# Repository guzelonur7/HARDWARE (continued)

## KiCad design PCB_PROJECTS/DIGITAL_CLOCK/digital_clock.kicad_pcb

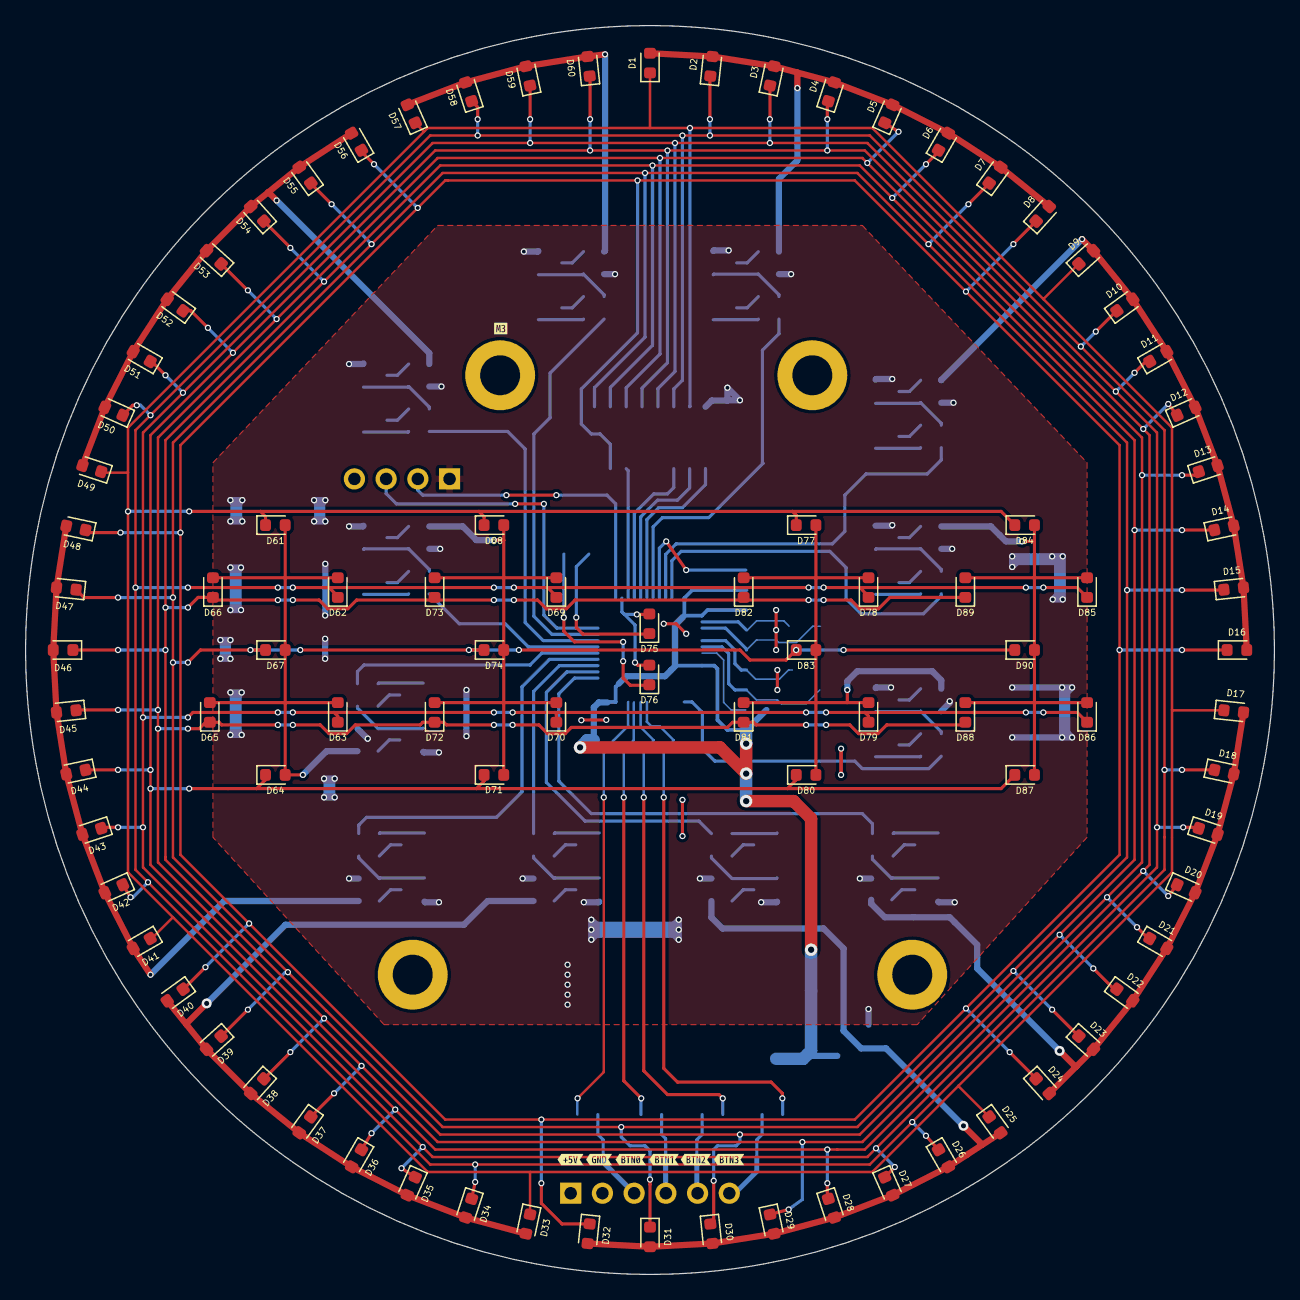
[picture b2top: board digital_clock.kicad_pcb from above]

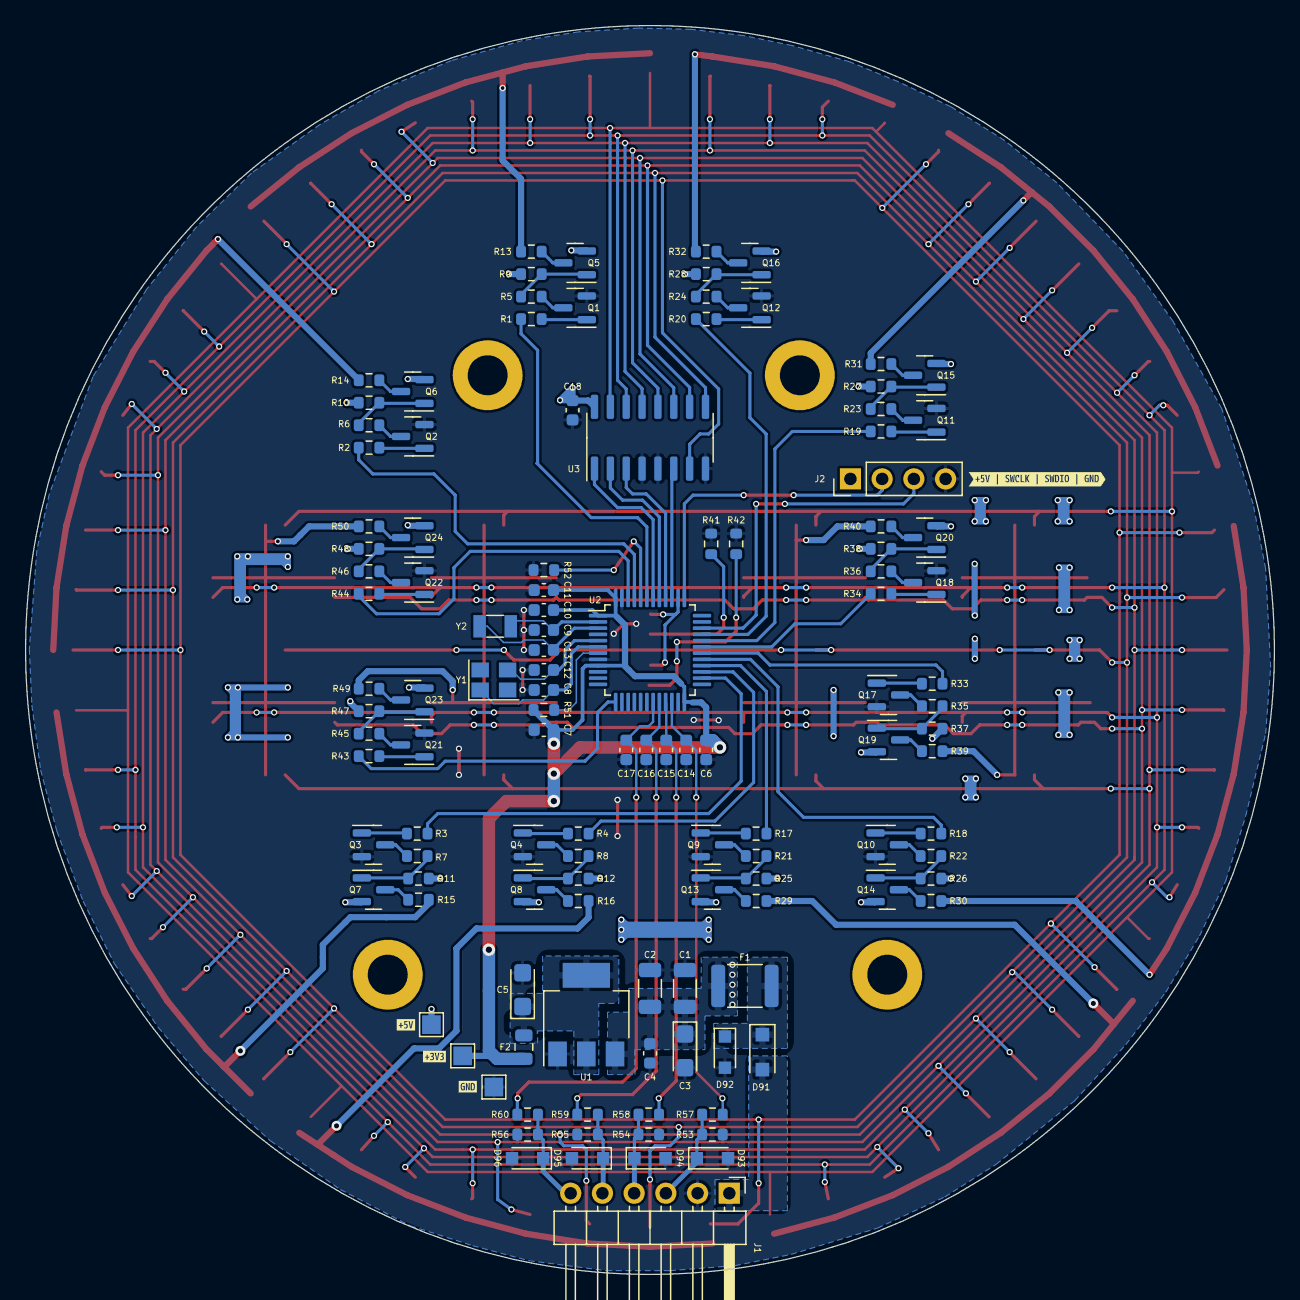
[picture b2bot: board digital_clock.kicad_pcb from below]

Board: 2 copper layers, 100.0 x 100.0 mm, 221 parts (124 on the bottom side), 109 nets.

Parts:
C1, C2: 47uF; C_1206_3216Metric
C3: 10uF; CP_EIA-3216-18_Kemet-A
C4, C7, C10, C11, C14, C15, C16, C17, C18: 100nF; C_0603_1608Metric
C5: 47uF; CP_EIA-3216-18_Kemet-A
C6: 4.7uF; C_0603_1608Metric
C8, C9, C12, C13: 12pF; C_0603_1608Metric
D1, D2, D3, D4, D5, D6, D7, D8, D9, D10, D11, D12, D13, D14, D15, D16, D17, D18, D19, D20, D21, D22, D23, D24, D25, D26, D27, D28, D29, D30, D31, D32, D33, D34, D35, D36, D37, D38, D39, D40, D41, D42, D43, D44, D45, D46, D47, D48, D49, D50, D51, D52, D53, D54, D55, D56, D57, D58, D59, D60, D61, D62, D63, D64, D65, D66, D67, D68, D69, D70, D71, D72, D73, D74, D75, D76, D77, D78, D79, D80, D81, D82, D83, D84, D85, D86, D87, D88, D89, D90: WHITE; LED_0603_1608Metric
D91: DS14W-HT; D_SOD-123F
D92: PESD5V0S1BA,115; D_SOD-323_HandSoldering
D93, D94, D95, D96: PESD3V3L1BA,115; D_SOD-323_HandSoldering
F1: 750mA; Fuse_1812_4532Metric
F2: 200mA; Fuse_0805_2012Metric
J1: Clock_Connector; PinHeader_1x06_P2.54mm_Horizontal
J2: Conn_01x04; PinHeader_1x04_P2.54mm_Vertical
Q1, Q2, Q3, Q4, Q9, Q10, Q11, Q12, Q17, Q18, Q21, Q22: BC817; SOT-23
Q5, Q6, Q7, Q8, Q13, Q14, Q15, Q16, Q19, Q20, Q23, Q24: BSS84; SOT-23
R1, R2, R3, R4, R17, R18, R19, R20, R33, R34, R43, R44: 470R; R_0603_1608Metric
R5, R6, R7, R8, R21, R22, R23, R24, R35, R36, R45, R46: 47R; R_0603_1608Metric
R9, R10, R11, R12, R25, R26, R27, R28, R37, R38, R47, R48: 120R; R_0603_1608Metric
R13, R14, R15, R16, R29, R30, R31, R32, R39, R40, R41, R42, R49, R50: 330R; R_0603_1608Metric
R51, R52, R53, R54, R55, R56, R57, R58, R59, R60: 10K; R_0603_1608Metric
TP1: +5V; TestPoint_Pad_1.5x1.5mm
TP2: GND; TestPoint_Pad_1.5x1.5mm
TP3: +3V3; TestPoint_Pad_1.5x1.5mm
U1: AMS1117-3.3; SOT-223-3_TabPin2
U2: STM32F030C6Tx; LQFP-48_7x7mm_P0.5mm
U3: 74HC138D; SOIC-16_3.9x9.9mm_P1.27mm
Y1: 32MHz; Crystal_SMD_SeikoEpson_FA238-4Pin_3.2x2.5mm
Y2: 32.768KHz; Crystal_SMD_3215-2Pin_3.2x1.5mm
kibuzzard-65DAF8A5: G***; kibuzzard-65DAF8A5
kibuzzard-65DAF8B6: G***; kibuzzard-65DAF8B6
kibuzzard-65DAF8BF: G***; kibuzzard-65DAF8BF
kibuzzard-65DAF8CD: G***; kibuzzard-65DAF8CD
kibuzzard-65DAF895: G***; kibuzzard-65DAF895
kibuzzard-65DAF967: G***; kibuzzard-65DAF967
kibuzzard-65DAFA7C: G***; kibuzzard-65DAFA7C
kibuzzard-65DAFAE3: G***; kibuzzard-65DAFAE3
kibuzzard-65DAFC06: G***; kibuzzard-65DAFC06
kibuzzard-65DAFC15: G***; kibuzzard-65DAFC15
kibuzzard-65DAFC20: G***; kibuzzard-65DAFC20

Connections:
/D0: U2.42 (PB6), U3.1 (A0)
/D1: U2.41 (PB5), U3.2 (A1)
/D2: U2.40 (PB4), U3.3 (A2)
/D3: U2.39 (PB3), U3.6 (G1)
/Decoder/+5V: C1.1, C2.1, C3.1, C4.1, C18.1, F1.1, J2.1, Q5.2 (S), Q6.2 (S), Q7.2 (S), Q8.2 (S), Q13.2 (S), Q14.2 (S), Q15.2 (S), Q16.2 (S), Q19.2 (S), Q20.2 (S), Q23.2 (S), Q24.2 (S), R9.1, R10.1, R11.1, R12.1, R25.1, R26.1, R27.1, R28.1, R37.1, R38.1, R47.1, R48.1, TP1.1, U1.3 (VI), U3.16 (VCC)
/Hour and Minute/DOTS: D75.2 (A), D76.2 (A), U2.38 (PA15)
/Hour and Minute/SW1_1: R33.2, U2.30 (PA9)
/Hour and Minute/SW1_2: R34.2, U2.31 (PA10)
/Hour and Minute/SW1_3: R43.2, U2.13 (PA3)
/Hour and Minute/SW1_4: R44.2, U2.46 (PB9)
/MCU/+3V3: C6.1, C7.1, C10.1, C11.1, F2.1, R51.2, TP3.1, U2.1 (VDD), U2.9 (VDDA), U2.24 (VDD), U2.48 (VDD)
/MCU/BOOT0: R52.2, U2.44 (BOOT0)
/MCU/BTN0_A: D93.1 (K), J1.3, R53.1, R57.1
/MCU/BTN0_B: C14.1, R57.2, U2.22 (PB11)
/MCU/BTN1_A: D94.1 (K), J1.4, R54.1, R58.1
/MCU/BTN1_B: C15.1, R58.2, U2.21 (PB10)
/MCU/BTN2_A: D95.1 (K), J1.5, R55.1, R59.1
/MCU/BTN2_B: C16.1, R59.2, U2.20 (PB2)
/MCU/BTN3_A: D96.1 (K), J1.6, R56.1, R60.1
/MCU/BTN3_B: C17.1, R60.2, U2.19 (PB1)
/MCU/NRST: R51.1, U2.7 (NRST)
/MCU/OSC32_IN: C13.1, U2.3 (PC14), Y2.2
/MCU/OSC32_OUT: C9.1, U2.2 (PC13), Y2.1
/MCU/OSC_IN: C12.1, U2.5 (PF0), Y1.3
/MCU/OSC_OUT: C8.1, U2.6 (PF1), Y1.1
/MCU/SW0_1: R1.2, U2.43 (PB7)
/MCU/SW0_2: R2.2, U2.45 (PB8)
/MCU/SW0_3: R3.2, U2.26 (PB13)
/MCU/SW0_4: R4.2, U2.27 (PB14)
/MCU/SW0_5: R17.2, U2.28 (PB15)
/MCU/SW0_6: R18.2, U2.29 (PA8)
/MCU/SW0_7: R19.2, U2.32 (PA11)
/MCU/SW0_8: R20.2, U2.33 (PA12)
/MCU/SWCLK: J2.2, U2.37 (PA14)
/MCU/SWDIO: J2.3, U2.34 (PA13)
/Power/+5V_IN: D91.2 (A), J1.1
/Y0: D1.1 (K), D9.1 (K), D17.1 (K), D25.1 (K), D33.1 (K), D41.1 (K), D49.1 (K), D57.1 (K), D61.1 (K), D68.1 (K), D77.1 (K), D84.1 (K), U3.15 (~Y0)
/Y1: D2.1 (K), D10.1 (K), D18.1 (K), D26.1 (K), D34.1 (K), D42.1 (K), D50.1 (K), D58.1 (K), D62.1 (K), D69.1 (K), D78.1 (K), D85.1 (K), U3.14 (~Y1)
/Y2: D3.1 (K), D11.1 (K), D19.1 (K), D27.1 (K), D35.1 (K), D43.1 (K), D51.1 (K), D59.1 (K), D63.1 (K), D70.1 (K), D79.1 (K), D86.1 (K), U3.13 (~Y2)
/Y3: D4.1 (K), D12.1 (K), D20.1 (K), D28.1 (K), D36.1 (K), D44.1 (K), D52.1 (K), D60.1 (K), D64.1 (K), D71.1 (K), D80.1 (K), D87.1 (K), U3.12 (~Y3)
/Y4: D5.1 (K), D13.1 (K), D21.1 (K), D29.1 (K), D37.1 (K), D45.1 (K), D53.1 (K), D65.1 (K), D72.1 (K), D81.1 (K), D88.1 (K), U3.11 (~Y4)
/Y5: D6.1 (K), D14.1 (K), D22.1 (K), D30.1 (K), D38.1 (K), D46.1 (K), D54.1 (K), D66.1 (K), D73.1 (K), D82.1 (K), D89.1 (K), U3.10 (~Y5)
/Y6: D7.1 (K), D15.1 (K), D23.1 (K), D31.1 (K), D39.1 (K), D47.1 (K), D55.1 (K), D67.1 (K), D74.1 (K), D83.1 (K), D90.1 (K), U3.9 (~Y6)
/Y7: D8.1 (K), D16.1 (K), D24.1 (K), D32.1 (K), D40.1 (K), D48.1 (K), D56.1 (K), U3.7 (~Y7)
GND: C1.2, C2.2, C3.2, C4.2, C5.2, C6.2, C7.2, C8.2, C9.2, C10.2, C11.2, C12.2, C13.2, C14.2, C15.2, C16.2, C17.2, C18.2, D92.2 (A), D93.2 (A), D94.2 (A), D95.2 (A), D96.2 (A), J1.2, J2.4, Q1.2 (E), Q2.2 (E), Q3.2 (E), Q4.2 (E), Q9.2 (E), Q10.2 (E), Q11.2 (E), Q12.2 (E), Q17.2 (E), Q18.2 (E), Q21.2 (E), Q22.2 (E), R41.1, R42.1, R52.1, R53.2, R54.2, R55.2, R56.2, TP2.1, U1.1 (GND), U2.8 (VSSA), U2.23 (VSS), U2.47 (VSS), U3.4 (~G2A), U3.5 (~G2B), U3.8 (GND)
unnamed: C5.1, F2.2, U1.2 (VO)
unnamed: D1.2 (A), D2.2 (A), D3.2 (A), D4.2 (A), D5.2 (A), D6.2 (A), D7.2 (A), D8.2 (A), R13.2
unnamed: D9.2 (A), D10.2 (A), D11.2 (A), D12.2 (A), D13.2 (A), D14.2 (A), D15.2 (A), D16.2 (A), R14.2
unnamed: D17.2 (A), D18.2 (A), D19.2 (A), D20.2 (A), D21.2 (A), D22.2 (A), D23.2 (A), D24.2 (A), R15.2
unnamed: D25.2 (A), D26.2 (A), D27.2 (A), D28.2 (A), D29.2 (A), D30.2 (A), D31.2 (A), D32.2 (A), R16.2
unnamed: D33.2 (A), D34.2 (A), D35.2 (A), D36.2 (A), D37.2 (A), D38.2 (A), D39.2 (A), D40.2 (A), R29.2
unnamed: D41.2 (A), D42.2 (A), D43.2 (A), D44.2 (A), D45.2 (A), D46.2 (A), D47.2 (A), D48.2 (A), R30.2
unnamed: D49.2 (A), D50.2 (A), D51.2 (A), D52.2 (A), D53.2 (A), D54.2 (A), D55.2 (A), D56.2 (A), R31.2
unnamed: D57.2 (A), D58.2 (A), D59.2 (A), D60.2 (A), R32.2
unnamed: D61.2 (A), D62.2 (A), D63.2 (A), D64.2 (A), D65.2 (A), D66.2 (A), D67.2 (A), R39.2
unnamed: D68.2 (A), D69.2 (A), D70.2 (A), D71.2 (A), D72.2 (A), D73.2 (A), D74.2 (A), R40.2
unnamed: D75.1 (K), R41.2
unnamed: D76.1 (K), R42.2
unnamed: D77.2 (A), D78.2 (A), D79.2 (A), D80.2 (A), D81.2 (A), D82.2 (A), D83.2 (A), R49.2
unnamed: D84.2 (A), D85.2 (A), D86.2 (A), D87.2 (A), D88.2 (A), D89.2 (A), D90.2 (A), R50.2
unnamed: D91.1 (K), D92.1 (K), F1.2
unnamed: Q1.1 (B), R1.1
unnamed: Q1.3 (C), R5.2
unnamed: Q2.1 (B), R2.1
unnamed: Q2.3 (C), R6.2
unnamed: Q3.1 (B), R3.1
unnamed: Q3.3 (C), R7.2
unnamed: Q4.1 (B), R4.1
unnamed: Q4.3 (C), R8.2
unnamed: Q5.1 (G), R5.1, R9.2
unnamed: Q5.3 (D), R13.1
unnamed: Q6.1 (G), R6.1, R10.2
unnamed: Q6.3 (D), R14.1
unnamed: Q7.1 (G), R7.1, R11.2
unnamed: Q7.3 (D), R15.1
unnamed: Q8.1 (G), R8.1, R12.2
unnamed: Q8.3 (D), R16.1
unnamed: Q9.1 (B), R17.1
unnamed: Q9.3 (C), R21.2
unnamed: Q10.1 (B), R18.1
unnamed: Q10.3 (C), R22.2
unnamed: Q11.1 (B), R19.1
unnamed: Q11.3 (C), R23.2
unnamed: Q12.1 (B), R20.1
unnamed: Q12.3 (C), R24.2
unnamed: Q13.1 (G), R21.1, R25.2
unnamed: Q13.3 (D), R29.1
unnamed: Q14.1 (G), R22.1, R26.2
unnamed: Q14.3 (D), R30.1
unnamed: Q15.1 (G), R23.1, R27.2
unnamed: Q15.3 (D), R31.1
unnamed: Q16.1 (G), R24.1, R28.2
unnamed: Q16.3 (D), R32.1
unnamed: Q17.1 (B), R33.1
unnamed: Q17.3 (C), R35.2
unnamed: Q18.1 (B), R34.1
unnamed: Q18.3 (C), R36.2
unnamed: Q19.1 (G), R35.1, R37.2
unnamed: Q19.3 (D), R39.1
unnamed: Q20.1 (G), R36.1, R38.2
unnamed: Q20.3 (D), R40.1
unnamed: Q21.1 (B), R43.1
unnamed: Q21.3 (C), R45.2
unnamed: Q22.1 (B), R44.1
unnamed: Q22.3 (C), R46.2
unnamed: Q23.1 (G), R45.1, R47.2
unnamed: Q23.3 (D), R49.1
unnamed: Q24.1 (G), R46.1, R48.2
unnamed: Q24.3 (D), R50.1

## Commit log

2025-03-22 First Commit.
2025-03-22 PCB Projects Added.
